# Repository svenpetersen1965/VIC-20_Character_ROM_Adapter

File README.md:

# VIC-20 Character ROM Adapter
A character ROM adapter for the Commodore VIC-20 for 27C64...512 EPROMs. It supports the usage of the 2nd 2332 ROM chip select for address decoding (which the <a href="https://github.com/svenpetersen1965/C64-CHARSET-Adaptor-Switch">C64 Character ROM Adapter</a> does not do.

It is configurable via solder bridges and can be configured as a C64 character ROM adapter, as well. It fits all VIC-20 mainboards and all C64 mainboards. It is a good solution for the C64 short board and a working solution for the C64 long boards. It might collide with a optional kernal adapter on the long boards, though, so the recommended solution for those is still the <a href="https://github.com/svenpetersen1965/C64-CHARSET-Adaptor-Switch">C64 Character ROM Adapter</a>.

The VIC-20 Character ROM Adapter was mainly created to provide a solution for the <a href="https://www.tindie.com/products/bobsbits/vicky-twenty-commodore-vic-20-pcb-replica/">Vicky Twenty</a> VIC-20 replica.

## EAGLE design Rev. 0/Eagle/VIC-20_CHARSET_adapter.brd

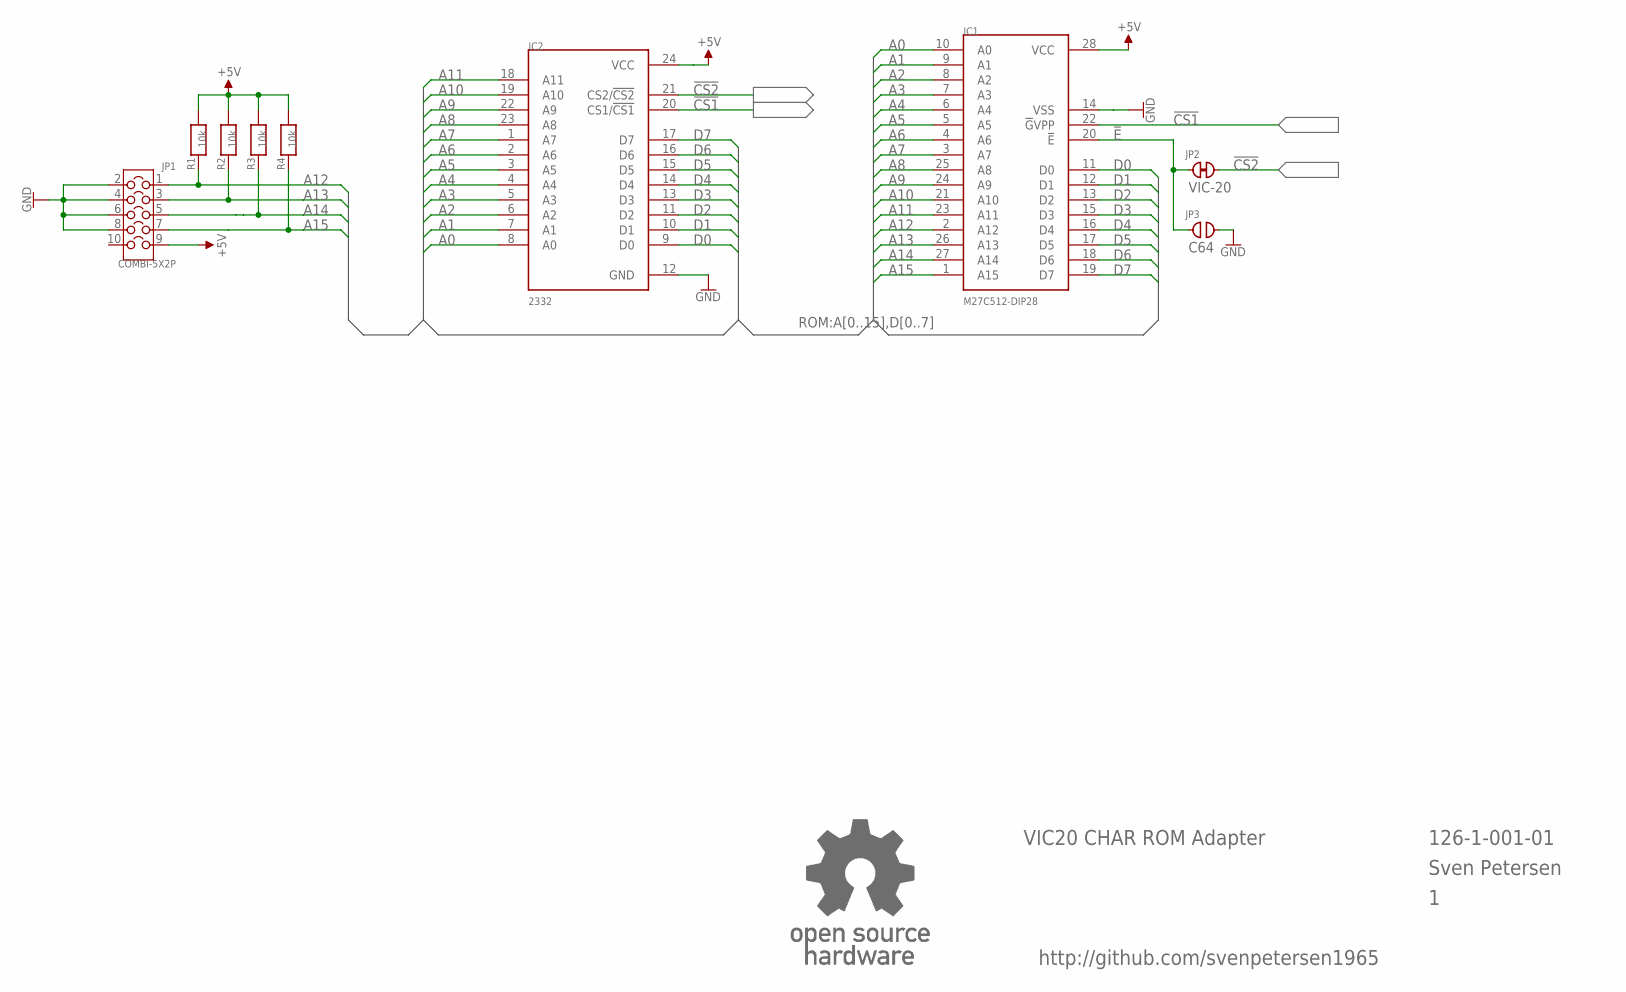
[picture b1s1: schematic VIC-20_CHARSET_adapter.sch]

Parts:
IC1: M27C512-DIP28; DIL28-6
IC2: 2332; DIL24_SOCKET
JP1: COMBI-5X2P; COMBI-5X2
JP2: CLOSED; CP_CL
JP3: OPEN; CP_OP
R1, R2, R3, R4: 10k; 0805
U$6: OPEN_SOURCE_HW; OPENHW

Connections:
!CS1: IC1.22 (!G!VPP), IC2.20 (CS1/!CS1)
!CS2: IC2.21 (CS2/!CS2), JP2.2
!E: IC1.20 (!E), JP2.1, JP3.1
+5V: IC1.28 (VCC), IC2.24 (VCC), JP1.9, R1.2, R2.2, R3.2, R4.2
A0: IC1.10 (A0), IC2.8 (A0)
A1: IC1.9 (A1), IC2.7 (A1)
A2: IC1.8 (A2), IC2.6 (A2)
A3: IC1.7 (A3), IC2.5 (A3)
A4: IC1.6 (A4), IC2.4 (A4)
A5: IC1.5 (A5), IC2.3 (A5)
A6: IC1.4 (A6), IC2.2 (A6)
A7: IC1.3 (A7), IC2.1 (A7)
A8: IC1.25 (A8), IC2.23 (A8)
A9: IC1.24 (A9), IC2.22 (A9)
A10: IC1.21 (A10), IC2.19 (A10)
A11: IC1.23 (A11), IC2.18 (A11)
A12: IC1.2 (A12), JP1.1, R1.1
A13: IC1.26 (A13), JP1.3, R2.1
A14: IC1.27 (A14), JP1.5, R3.1
A15: IC1.1 (A15), JP1.7, R4.1
D0: IC1.11 (D0), IC2.9 (D0)
D1: IC1.12 (D1), IC2.10 (D1)
D2: IC1.13 (D2), IC2.11 (D2)
D3: IC1.15 (D3), IC2.13 (D3)
D4: IC1.16 (D4), IC2.14 (D4)
D5: IC1.17 (D5), IC2.15 (D5)
D6: IC1.18 (D6), IC2.16 (D6)
D7: IC1.19 (D7), IC2.17 (D7)
GND: IC1.14 (VSS), IC2.12 (GND), JP1.2, JP1.4, JP1.6, JP1.8, JP3.2

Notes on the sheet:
126-1-001-01
Sven Petersen
VIC20 CHAR ROM Adapter
http://github.com/svenpetersen1965
VIC-20
C64

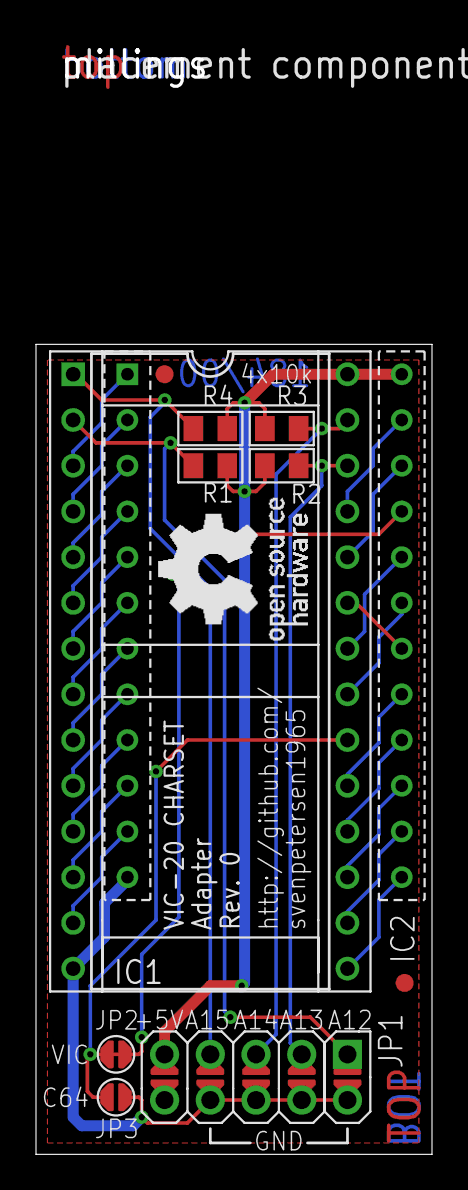
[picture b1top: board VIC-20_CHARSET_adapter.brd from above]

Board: 2 copper layers, 22.0 x 45.0 mm, 16 parts (1 on the bottom side), 29 nets.

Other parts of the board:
U$11: SVEN_TAG
U$16: GS28P
U$17, U$18: SMD_REF_R1MM
U$19: 2LAYER
U$20: PCB-TITLE/

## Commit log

2021-07-18 Initial Release
